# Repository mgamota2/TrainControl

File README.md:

# TrainControl

## Hardware

Wall Adapter - 18V DC Output
https://www.digikey.com/en/products/detail/triad-magnetics/WSU180-1000/3094965

Power Plug
https://www.digikey.com/en/products/detail/w%C3%BCrth-elektronik/694106301002/5047522

L293D H-Bridge
https://www.digikey.com/en/products/detail/stmicroelectronics/L293D/634700

18V-5V Converter
https://www.digikey.com/en/products/detail/mornsun-america-llc/URB4805S-3WR3/16348323

Raspberry Pi Pico W
https://www.digikey.com/en/products/detail/raspberry-pi/SC0918/16608263

MOSFETs(NMOS)
https://www.mouser.com/ProductDetail/Panjit/PJA3404_R1_00001?qs=sPbYRqrBIVkiUO9ZInE3tw%3D%3D

Cap(100uF)
https://www.digikey.com/en/products/detail/panasonic-electronic-components/ECA-1HM101B/268482

Cap(0.1uF)
https://www.mouser.com/ProductDetail/KEMET/C1210C104K1RAC?qs=0OaNwhvMTe1%2FSOzgnjC6ew%3D%3D

Cap(1 uF)
https://www.mouser.com/ProductDetail/Samsung-Electro-Mechanics/CL32B105KBHNNNE?qs=349EhDEZ59rXY4nCVEMdbA%3D%3D

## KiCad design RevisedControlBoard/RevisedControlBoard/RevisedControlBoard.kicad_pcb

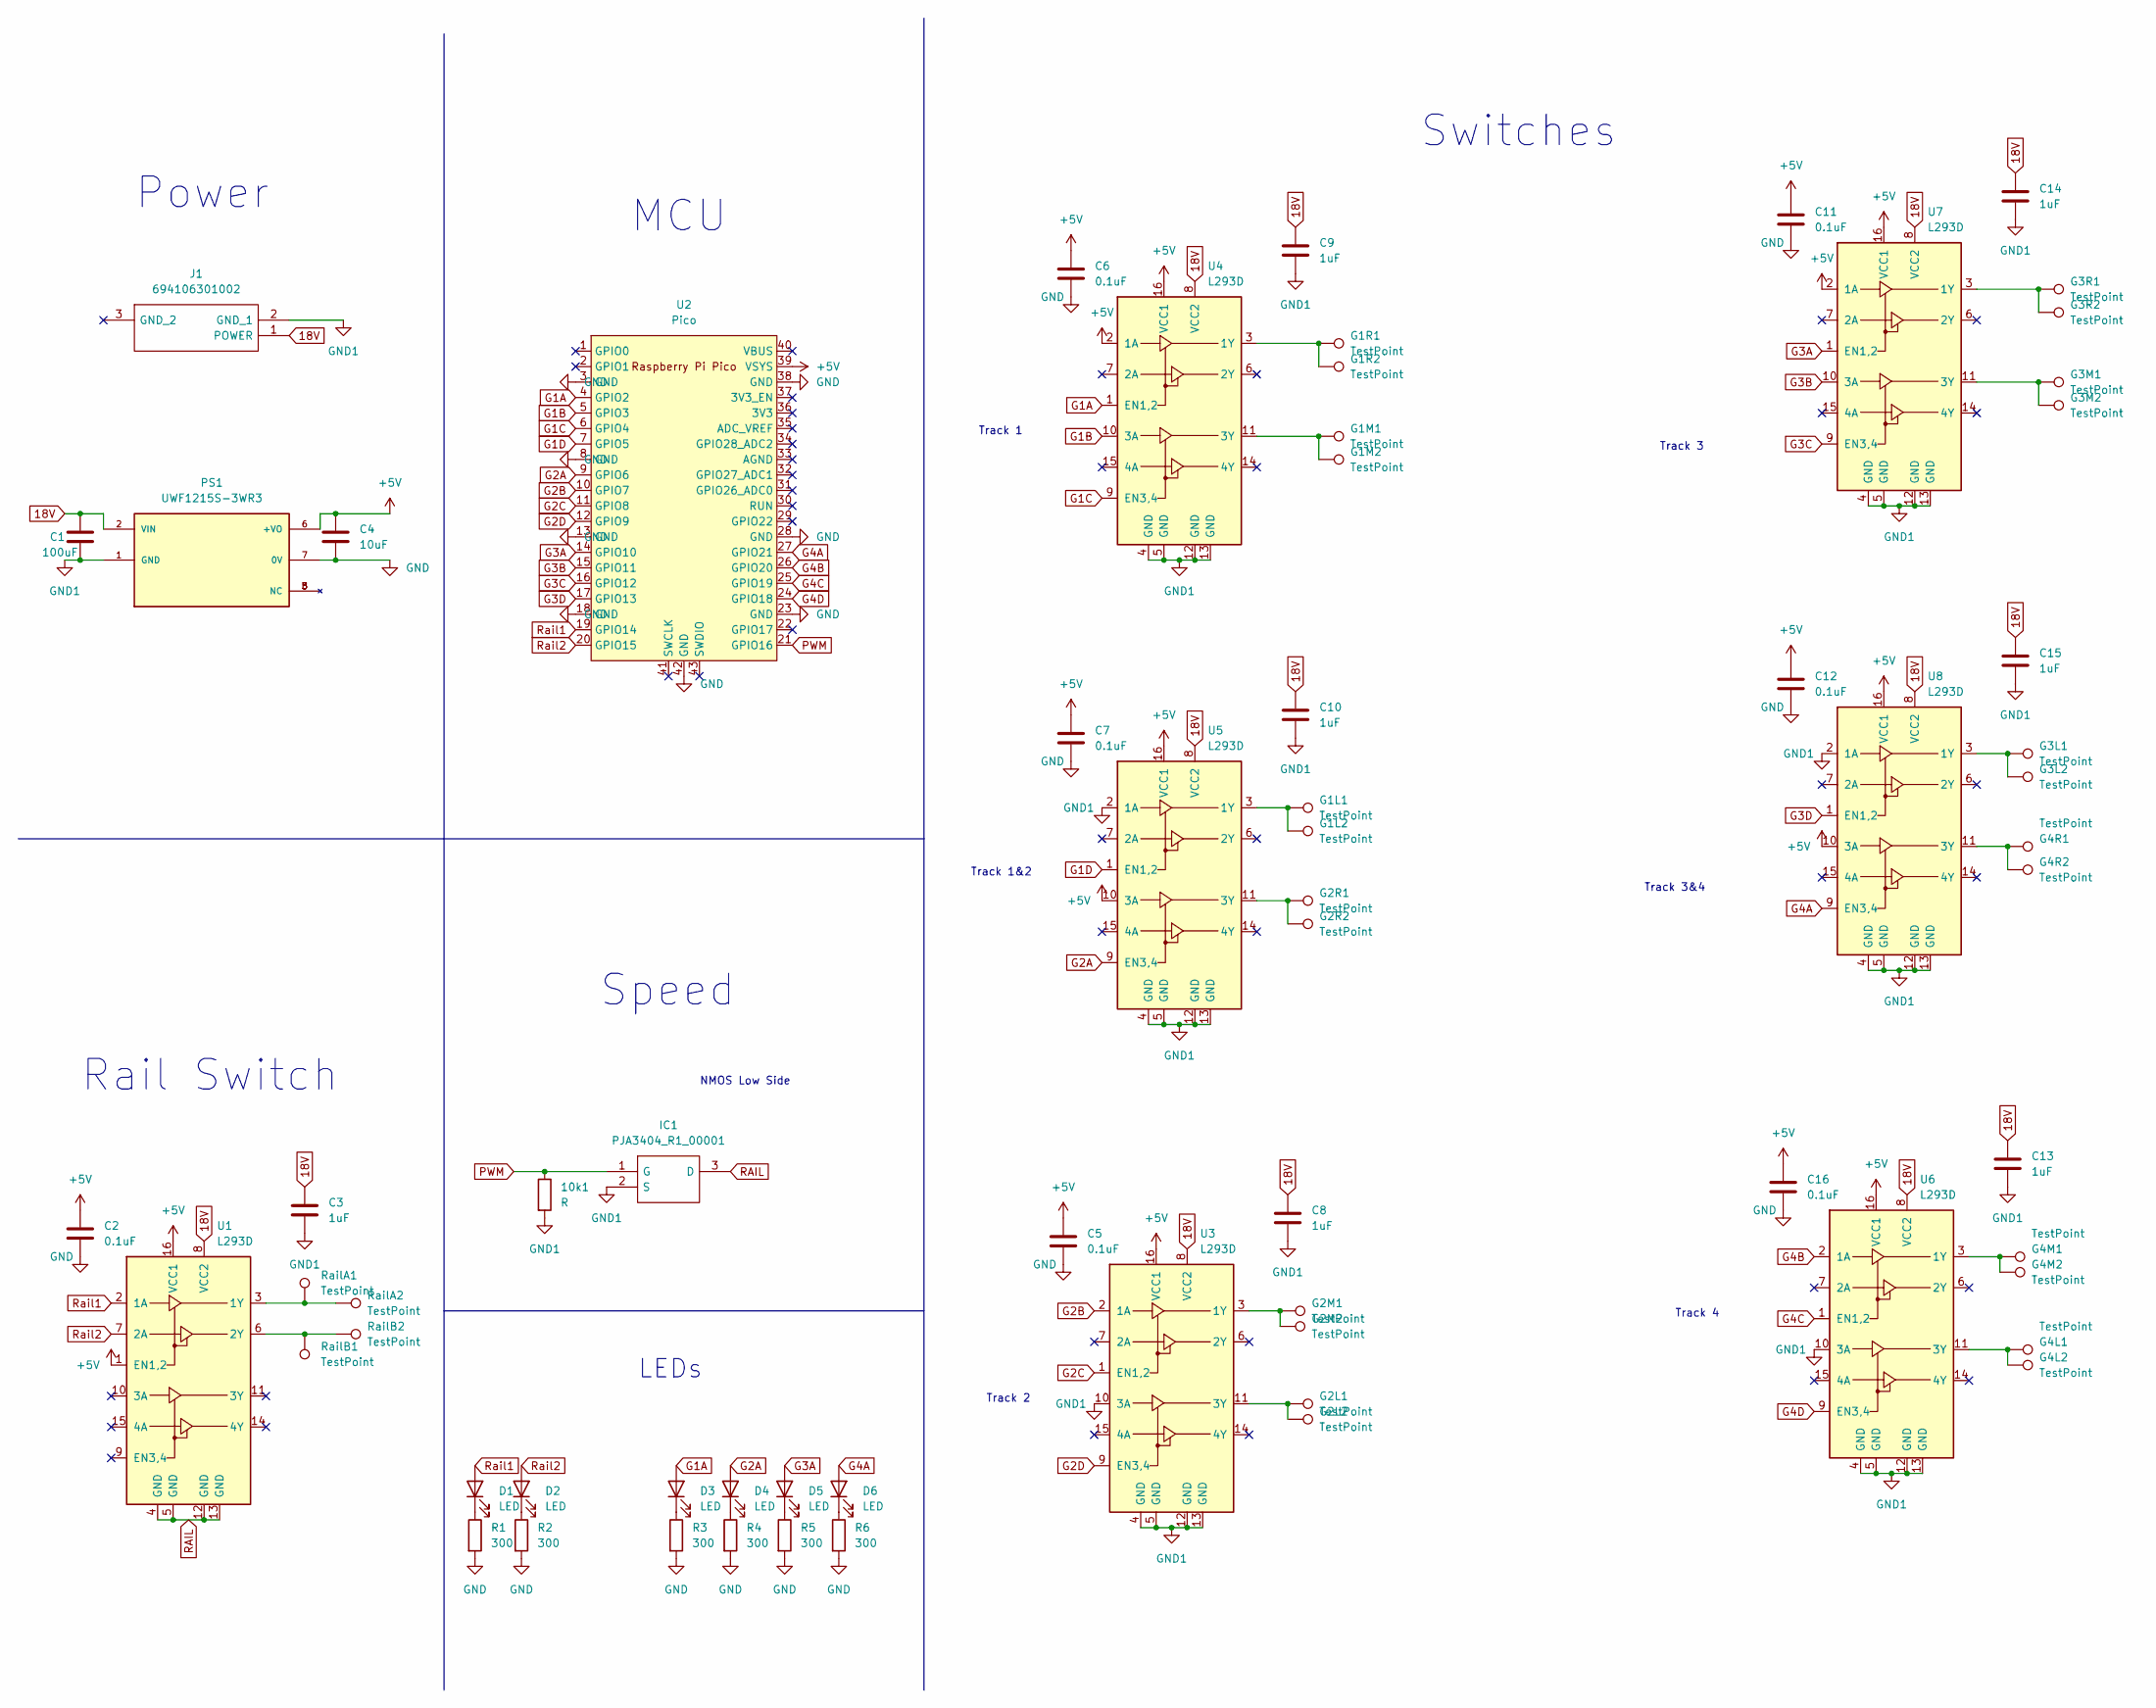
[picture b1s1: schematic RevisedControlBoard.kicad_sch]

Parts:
10k1: R; R_Axial_DIN0204_L3.6mm_D1.6mm_P7.62mm_Horizontal
C1: 100uF; CP_Radial_D10.0mm_P7.50mm
C2, C5, C6, C7, C11, C12, C16: 0.1uF; C_1210_3225Metric
C3, C8, C9, C10, C13, C14, C15: 1uF; C_1210_3225Metric
C4: 10uF; CP_Radial_D10.0mm_P7.50mm
D1, D2, D3, D4, D5, D6: LED; LED_D3.0mm
G1L1, G1L2, G1M1, G1M2, G1R1, G1R2, G2L1, G2L2, G2M1, G2M2, G2R1, G2R2, G3L1, G3L2, G3M1, G3M2, G3R1, G3R2, G4L1, G4L2, G4M1, G4M2, G4R1, G4R2: TestPoint; TestPoint_Pad_2.5x2.5mm
IC1: PJA3404_R1_00001; SOT95P240X110-3N; Mouser Part Number 241-PJA3404_R1_00001
J1: 694106301002; 694106301002_1; Mouser Part Number 710-694106301002
PS1: UWF1215S-3WR3; CONV_UWF1215S-3WR3; PARTREV 2020.08.11-A/1
R1, R2, R3, R4, R5, R6: 300; R_Axial_DIN0204_L3.6mm_D1.6mm_P7.62mm_Horizontal
RailA1, RailA2: TestPoint; TestPoint_Pad_2.5x2.5mm
RailB1, RailB2: TestPoint; TestPoint_Pad_2.5x2.5mm
U1, U3, U4, U5, U6, U7, U8: L293D; DIP-16_W7.62mm
U2: Pico; RPi_Pico_SMD_TH

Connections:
18V: C1.1, C3.1, C8.1, C9.1, C10.1, C13.1, C14.1, C15.1, J1.1 (POWER), PS1.2 (VIN), U1.8 (VCC2), U3.8 (VCC2), U4.8 (VCC2), U5.8 (VCC2), U6.8 (VCC2), U7.8 (VCC2), U8.8 (VCC2)
+5V: C2.1, C4.1, C5.1, C6.1, C7.1, C11.1, C12.1, C16.1, PS1.6 (+VO), U1.1 (EN1,2), U1.16 (VCC1), U2.39 (VSYS), U3.16 (VCC1), U4.2 (1A), U4.16 (VCC1), U5.10 (3A), U5.16 (VCC1), U6.16 (VCC1), U7.2 (1A), U7.16 (VCC1), U8.10 (3A), U8.16 (VCC1)
G1A: D3.2 (A), U2.4 (GPIO2), U4.1 (EN1,2)
G1B: U2.5 (GPIO3), U4.10 (3A)
G1C: U2.6 (GPIO4), U4.9 (EN3,4)
G1D: U2.7 (GPIO5), U5.1 (EN1,2)
G2A: D4.2 (A), U2.9 (GPIO6), U5.9 (EN3,4)
G2B: U2.10 (GPIO7), U3.2 (1A)
G2C: U2.11 (GPIO8), U3.1 (EN1,2)
G2D: U2.12 (GPIO9), U3.9 (EN3,4)
G3A: D5.2 (A), U2.14 (GPIO10), U7.1 (EN1,2)
G3B: U2.15 (GPIO11), U7.10 (3A)
G3C: U2.16 (GPIO12), U7.9 (EN3,4)
G3D: U2.17 (GPIO13), U8.1 (EN1,2)
G4A: D6.2 (A), U2.27 (GPIO21), U8.9 (EN3,4)
G4B: U2.26 (GPIO20), U6.2 (1A)
G4C: U2.25 (GPIO19), U6.1 (EN1,2)
G4D: U2.24 (GPIO18), U6.9 (EN3,4)
GND: C2.2, C4.2, C5.2, C6.2, C7.2, C11.2, C12.2, C16.2, PS1.7 (0V), R1.2, R2.2, R3.2, R4.2, R5.2, R6.2, U2.3 (GND), U2.8 (GND), U2.13 (GND), U2.18 (GND), U2.23 (GND), U2.28 (GND), U2.38 (GND), U2.42 (GND)
GND1: 10k1.2, C1.2, C3.2, C8.2, C9.2, C10.2, C13.2, C14.2, C15.2, IC1.2 (S), J1.2 (GND_1), PS1.1 (GND), U3.4 (GND), U3.5 (GND), U3.10 (3A), U3.12 (GND), U3.13 (GND), U4.4 (GND), U4.5 (GND), U4.12 (GND), U4.13 (GND), U5.2 (1A), U5.4 (GND), U5.5 (GND), U5.12 (GND), U5.13 (GND), U6.4 (GND), U6.5 (GND), U6.10 (3A), U6.12 (GND), U6.13 (GND), U7.4 (GND), U7.5 (GND), U7.12 (GND), U7.13 (GND), U8.2 (1A), U8.4 (GND), U8.5 (GND), U8.12 (GND), U8.13 (GND)
unnamed: D1.1 (K), R1.1
unnamed: D2.1 (K), R2.1
unnamed: D3.1 (K), R3.1
unnamed: D4.1 (K), R4.1
unnamed: D5.1 (K), R5.1
unnamed: D6.1 (K), R6.1
unnamed: G1L1.1, G1L2.1, U5.3 (1Y)
unnamed: G1M1.1, G1M2.1, U4.11 (3Y)
unnamed: G1R1.1, G1R2.1, U4.3 (1Y)
unnamed: G2L1.1, G2L2.1, U3.11 (3Y)
unnamed: G2M1.1, G2M2.1, U3.3 (1Y)
unnamed: G2R1.1, G2R2.1, U5.11 (3Y)
unnamed: G3L1.1, G3L2.1, U8.3 (1Y)
unnamed: G3M1.1, G3M2.1, U7.11 (3Y)
unnamed: G3R1.1, G3R2.1, U7.3 (1Y)
unnamed: G4L1.1, G4L2.1, U6.11 (3Y)
unnamed: G4M1.1, G4M2.1, U6.3 (1Y)
unnamed: G4R1.1, G4R2.1, U8.11 (3Y)
unnamed: RailA1.1, RailA2.1, U1.3 (1Y)
unnamed: RailB1.1, RailB2.1, U1.6 (2Y)
PWM: 10k1.1, IC1.1 (G), U2.21 (GPIO16)
RAIL: IC1.3 (D), U1.4 (GND), U1.5 (GND), U1.12 (GND), U1.13 (GND)
Rail1: D1.2 (A), U1.2 (1A), U2.19 (GPIO14)
Rail2: D2.2 (A), U1.7 (2A), U2.20 (GPIO15)

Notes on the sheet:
MCU
Power
LEDs
Track 1&2
Track 3&4
Track 3
Track 2
Switches
Track 4
Track 1
NMOS Low Side
Speed
Rail Switch

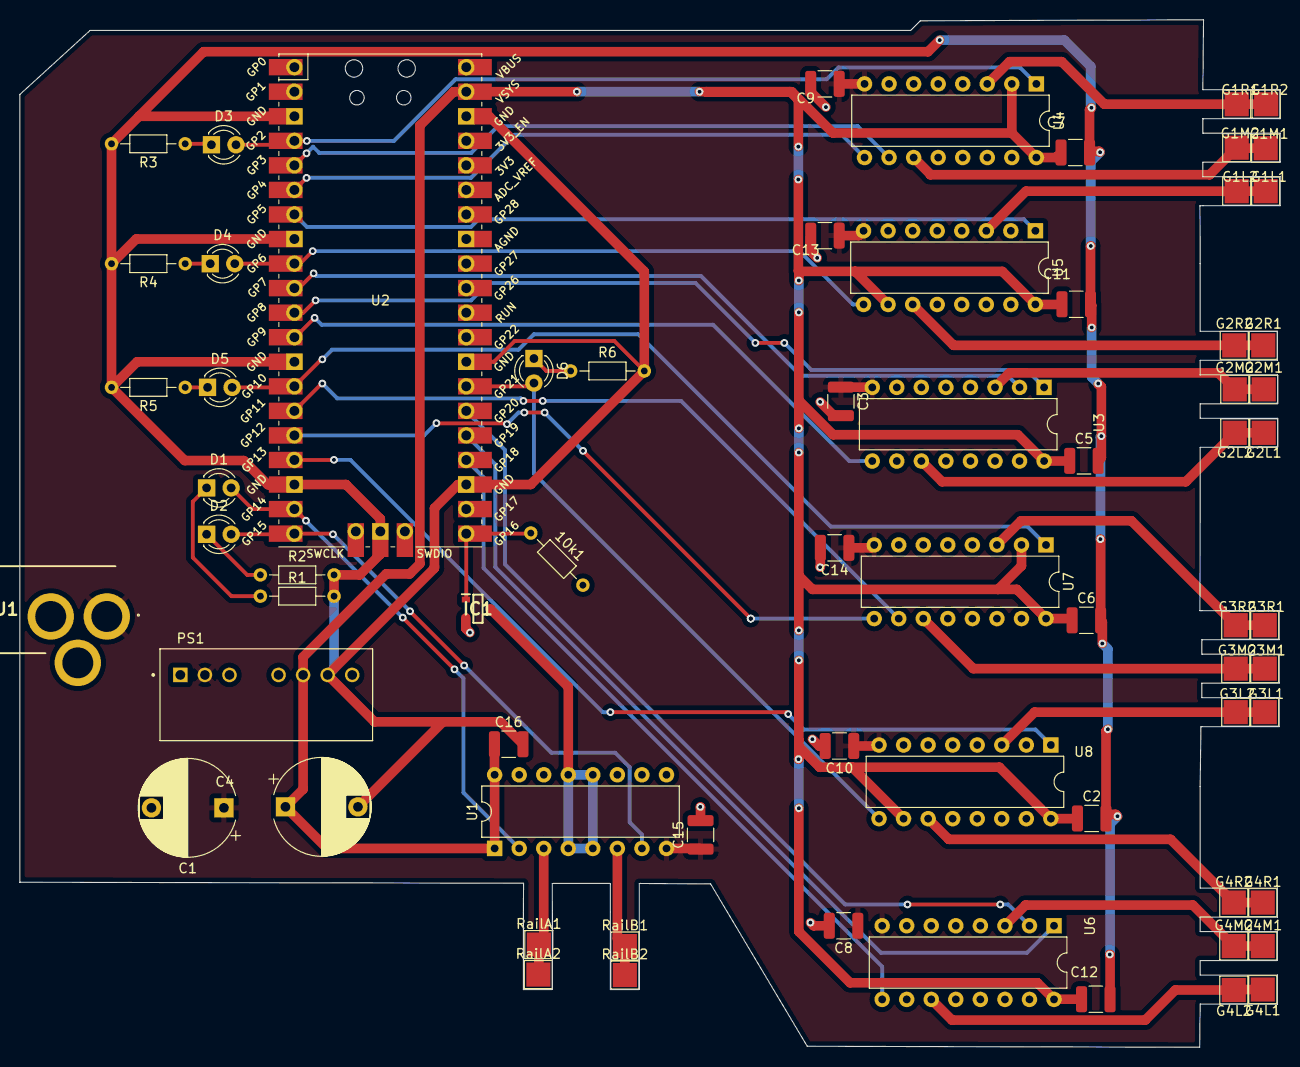
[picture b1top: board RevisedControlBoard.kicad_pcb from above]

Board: 2 copper layers, 130.4 x 106.3 mm, 68 parts (0 on the bottom side), 44 nets.

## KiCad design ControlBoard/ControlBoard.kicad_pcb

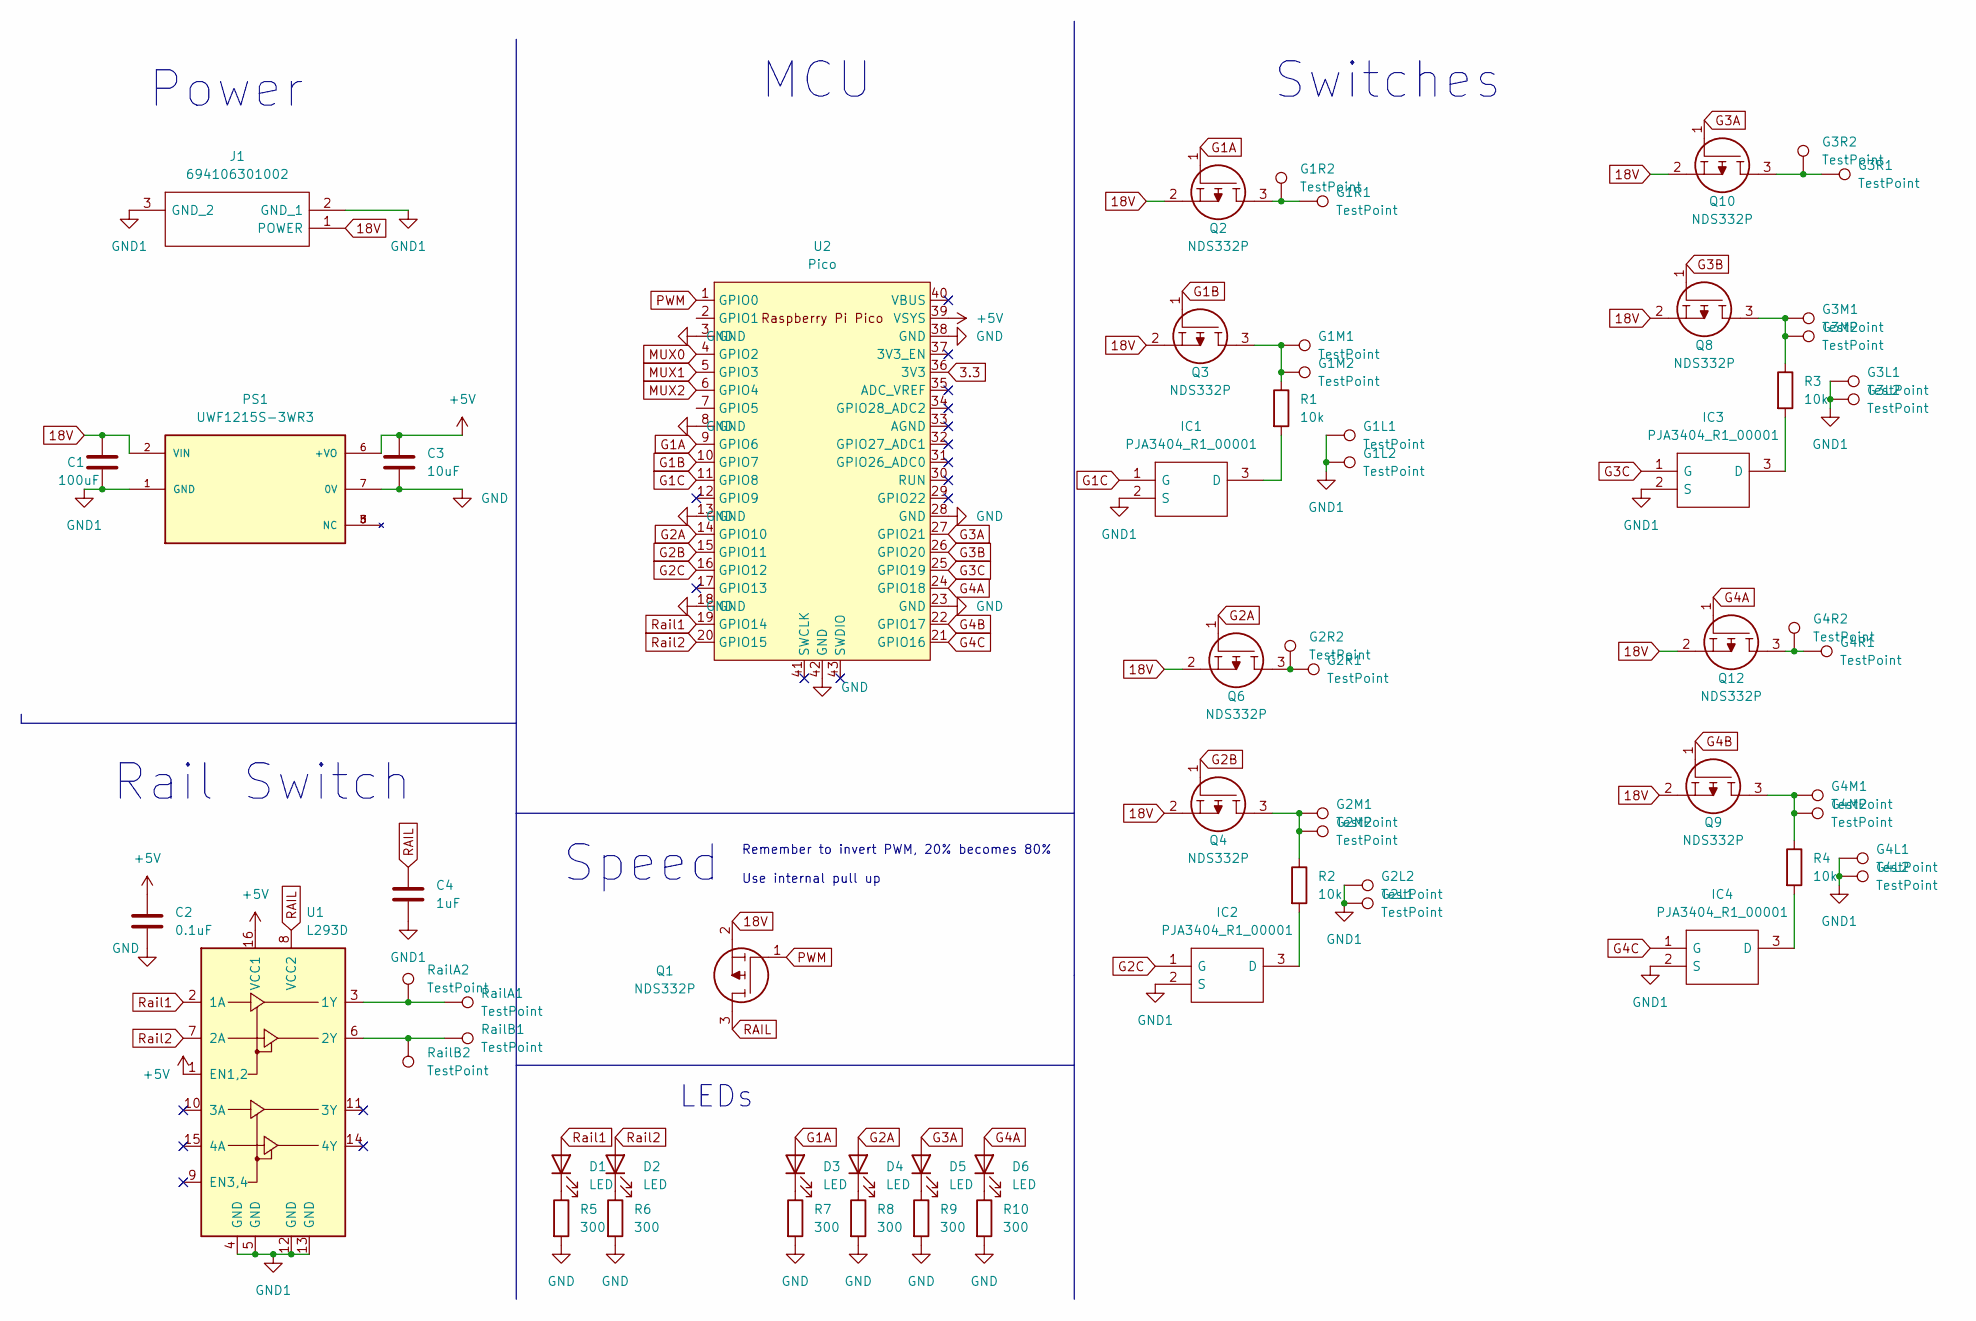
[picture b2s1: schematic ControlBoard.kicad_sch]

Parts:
C1: 100uF; CP_Radial_D10.0mm_P7.50mm
C2: 0.1uF; CP_Radial_D10.0mm_P7.50mm
C3: 10uF; CP_Radial_D10.0mm_P7.50mm
C4: 1uF; CP_Radial_D10.0mm_P7.50mm
D1, D2, D3, D4, D5, D6: LED; LED_D3.0mm
G1L1, G1L2, G1M1, G1M2, G1R1, G1R2, G2L1, G2L2, G2M1, G2M2, G2R1, G2R2, G3L1, G3L2, G3M1, G3M2, G3R1, G3R2, G4L1, G4L2, G4M1, G4M2, G4R1, G4R2: TestPoint; TestPoint_Pad_2.5x2.5mm
IC1, IC2, IC3, IC4: PJA3404_R1_00001; SOT95P240X110-3N; Mouser Part Number 241-PJA3404_R1_00001
J1: 694106301002; 694106301002_1; Mouser Part Number 710-694106301002
PS1: UWF1215S-3WR3; CONV_UWF1215S-3WR3; PARTREV 2020.08.11-A/1
Q1, Q2, Q3, Q4, Q6, Q8, Q9, Q10, Q12: NDS332P; SOT95P237X112-3N; Mouser Part Number 512-NDS332P
R1, R2, R3, R4: 10k; R_Axial_DIN0204_L3.6mm_D1.6mm_P7.62mm_Horizontal
R5, R6, R7, R8, R9, R10: 300; R_Axial_DIN0204_L3.6mm_D1.6mm_P7.62mm_Horizontal
RailA1, RailA2: TestPoint; TestPoint_Pad_2.5x2.5mm
RailB1, RailB2: TestPoint; TestPoint_Pad_2.5x2.5mm
U1: L293D; DIP-16_W7.62mm
U2: Pico; RPi_Pico_SMD_TH

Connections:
3.3: U2.36 (3V3)
18V: C1.1, J1.1 (POWER), PS1.2 (VIN), Q1.2, Q2.2, Q3.2, Q4.2, Q6.2, Q8.2, Q9.2, Q10.2, Q12.2
+5V: C2.1, C3.1, PS1.6 (+VO), U1.1 (EN1,2), U1.16 (VCC1), U2.39 (VSYS)
G1A: D3.2 (A), Q2.1, U2.9 (GPIO6)
G1B: Q3.1, U2.10 (GPIO7)
G1C: IC1.1 (G), U2.11 (GPIO8)
G2A: D4.2 (A), Q6.1, U2.14 (GPIO10)
G2B: Q4.1, U2.15 (GPIO11)
G2C: IC2.1 (G), U2.16 (GPIO12)
G3A: D5.2 (A), Q10.1, U2.27 (GPIO21)
G3B: Q8.1, U2.26 (GPIO20)
G3C: IC3.1 (G), U2.25 (GPIO19)
G4A: D6.2 (A), Q12.1, U2.24 (GPIO18)
G4B: Q9.1, U2.22 (GPIO17)
G4C: IC4.1 (G), U2.21 (GPIO16)
GND: C2.2, C3.2, PS1.7 (0V), R5.2, R6.2, R7.2, R8.2, R9.2, R10.2, U2.3 (GND), U2.8 (GND), U2.13 (GND), U2.18 (GND), U2.23 (GND), U2.28 (GND), U2.38 (GND), U2.42 (GND)
GND1: C1.2, C4.2, G1L1.1, G1L2.1, G2L1.1, G2L2.1, G3L1.1, G3L2.1, G4L1.1, G4L2.1, IC1.2 (S), IC2.2 (S), IC3.2 (S), IC4.2 (S), J1.2 (GND_1), J1.3 (GND_2), PS1.1 (GND), U1.4 (GND), U1.5 (GND), U1.12 (GND), U1.13 (GND)
MUX0: U2.4 (GPIO2)
MUX1: U2.5 (GPIO3)
MUX2: U2.6 (GPIO4)
unnamed: D1.1 (K), R5.1
unnamed: D2.1 (K), R6.1
unnamed: D3.1 (K), R7.1
unnamed: D4.1 (K), R8.1
unnamed: D5.1 (K), R9.1
unnamed: D6.1 (K), R10.1
unnamed: G1M1.1, G1M2.1, Q3.3, R1.1
unnamed: G1R1.1, G1R2.1, Q2.3
unnamed: G2M1.1, G2M2.1, Q4.3, R2.1
unnamed: G2R1.1, G2R2.1, Q6.3
unnamed: G3M1.1, G3M2.1, Q8.3, R3.1
unnamed: G3R1.1, G3R2.1, Q10.3
unnamed: G4M1.1, G4M2.1, Q9.3, R4.1
unnamed: G4R1.1, G4R2.1, Q12.3
unnamed: IC1.3 (D), R1.2
unnamed: IC2.3 (D), R2.2
unnamed: IC3.3 (D), R3.2
unnamed: IC4.3 (D), R4.2
unnamed: RailA1.1, RailA2.1, U1.3 (1Y)
unnamed: RailB1.1, RailB2.1, U1.6 (2Y)
PWM: Q1.1, U2.1 (GPIO0)
RAIL: C4.1, Q1.3, U1.8 (VCC2)
Rail1: D1.2 (A), U1.2 (1A), U2.19 (GPIO14)
Rail2: D2.2 (A), U1.7 (2A), U2.20 (GPIO15)

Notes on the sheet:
Remember to invert PWM, 20% becomes 80% Use internal pull up
MCU
Power
Speed
Switches
Rail Switch
LEDs

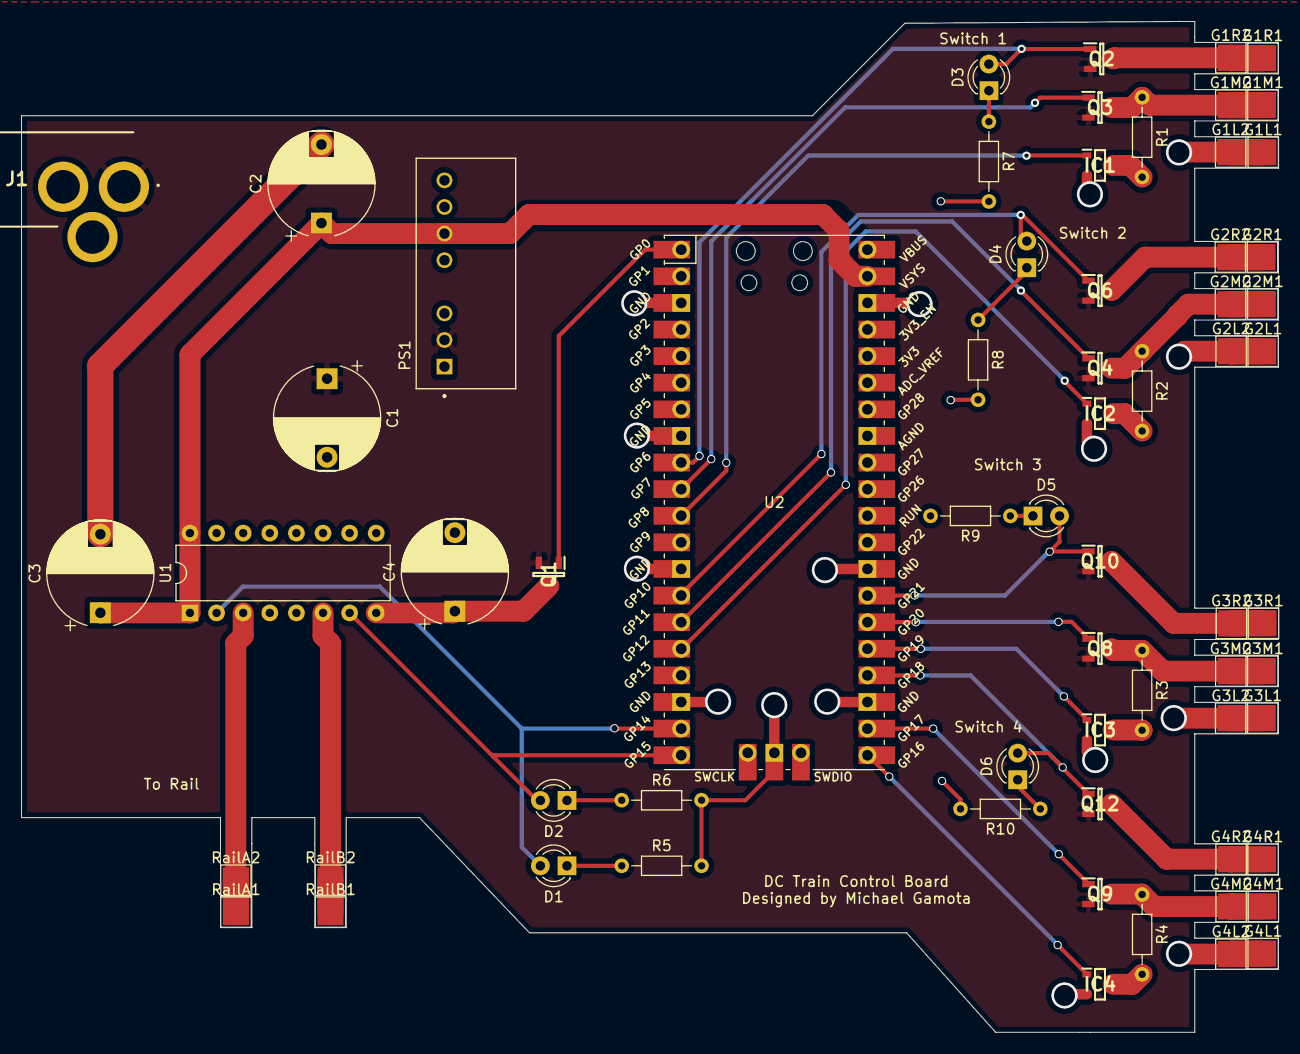
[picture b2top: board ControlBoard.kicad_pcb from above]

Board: 2 copper layers, 120.0 x 96.5 mm, 65 parts (0 on the bottom side), 40 nets.

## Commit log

2022-12-24 Shopping List
2022-12-24 Final parts list
2022-12-25 Finalized layout
2022-12-25 Ordered
2023-01-13 Added revised
2023-01-13 Updated BOM
